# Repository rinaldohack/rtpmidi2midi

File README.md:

# rtpmidi2midi
rtpMIDI to MIDI converter based on ESP8266

basically, you need ESP8266 as boards for arduino, lathoub AppleMIDI library, and FortySeven MIDI Library. 
the eagle files are also available. This code was tested on Wemos D1 Mini and ESP-01. 

Note : not all functions were implemented. The one that were tested intensively are MIDI Note and MIDI CC.

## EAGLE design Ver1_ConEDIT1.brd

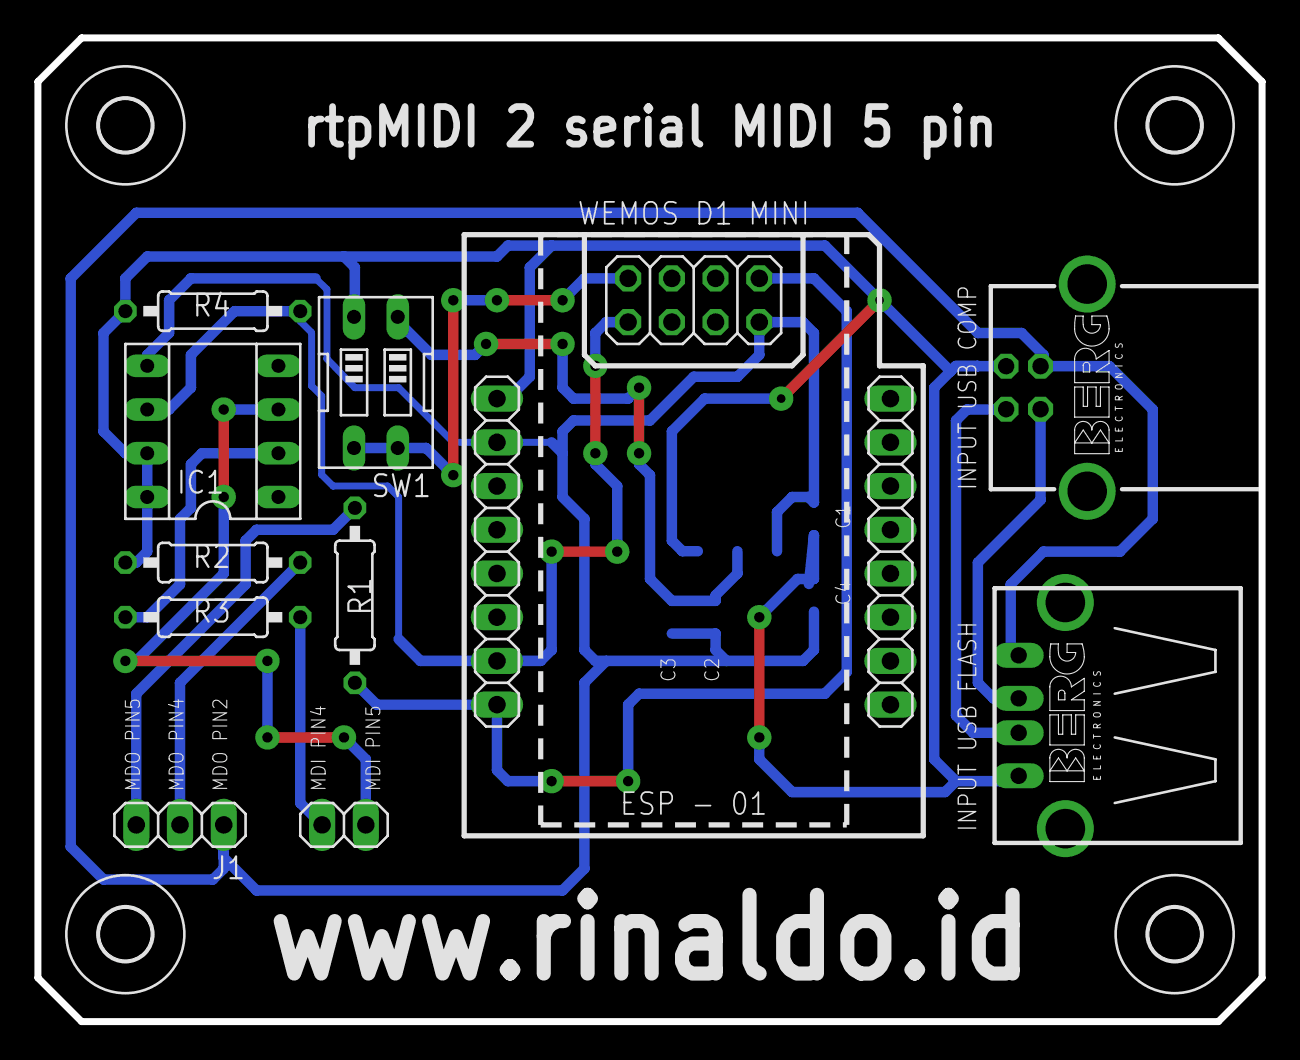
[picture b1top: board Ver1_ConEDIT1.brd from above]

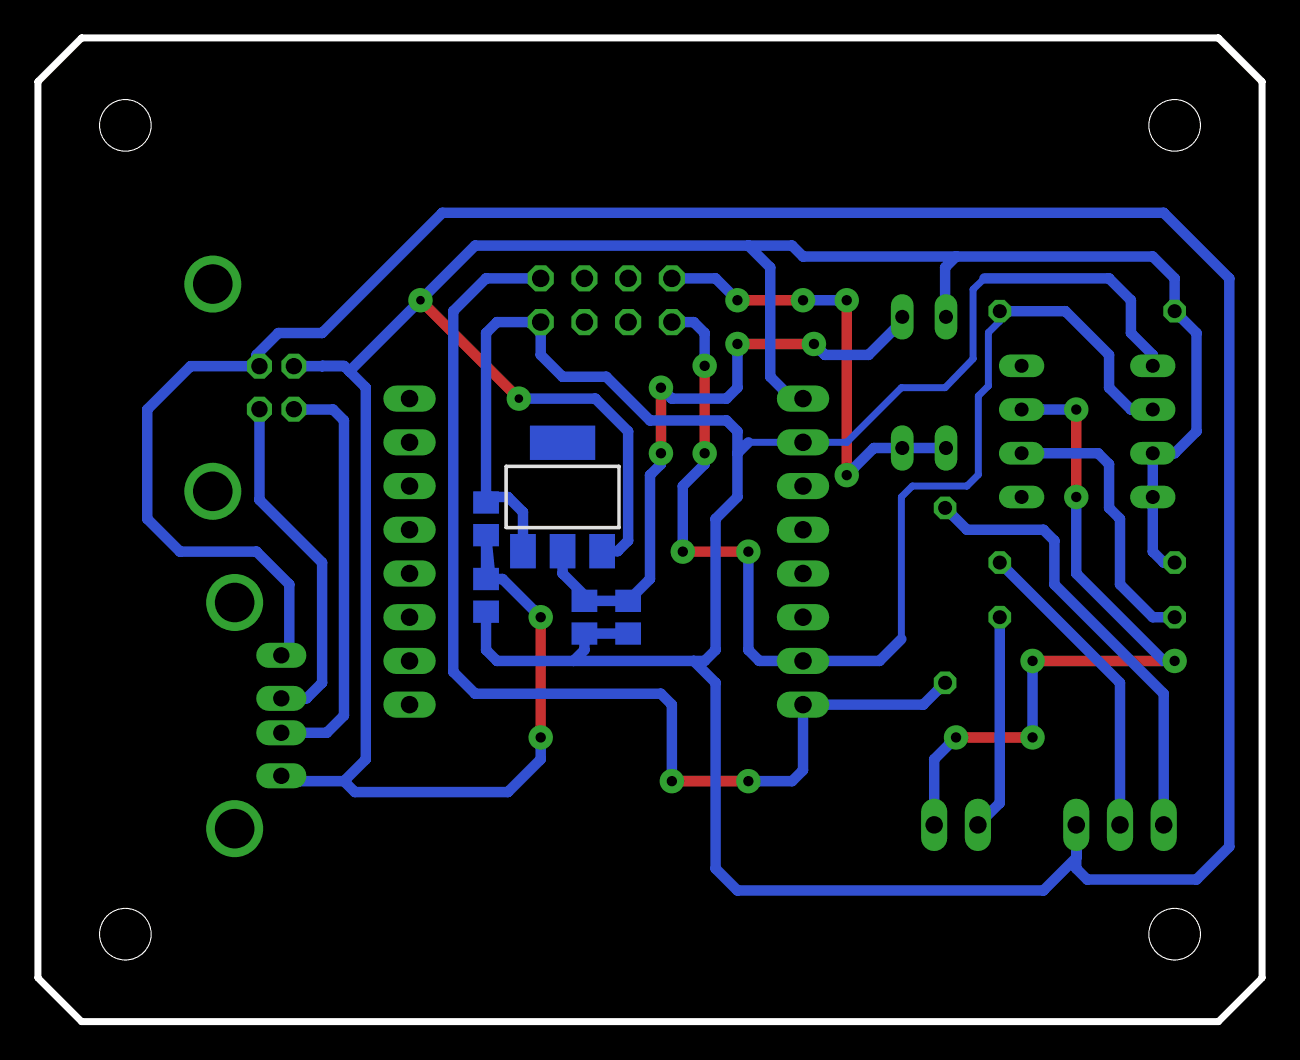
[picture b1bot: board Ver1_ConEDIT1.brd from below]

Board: 2 copper layers, 71.1 x 57.1 mm, 22 parts (5 on the bottom side), 13 nets.

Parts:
E$1: 2X04
E$2: 1X02
E$3: PN61729-S
E$4, E$7: 1X08
E$6: PN87520-S
E$11: SOT223
E$12, E$13, E$15, E$16: C0805
E$14, E$17, E$18, E$19: 3,0
IC1: SOCKET-08
J1: 1X03
R1, R2, R3, R4: 0207/10
SW1: EDG-02

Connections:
GND: E$3.4, E$6.4, E$11.1, E$12.2, E$13.2, E$15.2, E$16.1, IC1.5, J1.1
S$1: IC1.2, R3.1
S$2: E$11.2, E$12.1, E$15.1
S$3: IC1.6, R4.2
S$4: E$1.2, SW1.3, SW1.4
S$6: J1.3, R1.1
S$7: E$4.1, R1.2
S$8: J1.2, R2.1
S$10: E$3.2, E$6.2
S$11: E$3.3, E$6.3
S$12: E$2.2, IC1.3
S$13: E$2.1, R3.2
S$14: E$3.1, E$6.1, E$11.3, E$13.1, E$16.2, IC1.7, IC1.8, R2.2, R4.1

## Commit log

2019-08-12 schematics
2019-08-12 Update LICENSE
